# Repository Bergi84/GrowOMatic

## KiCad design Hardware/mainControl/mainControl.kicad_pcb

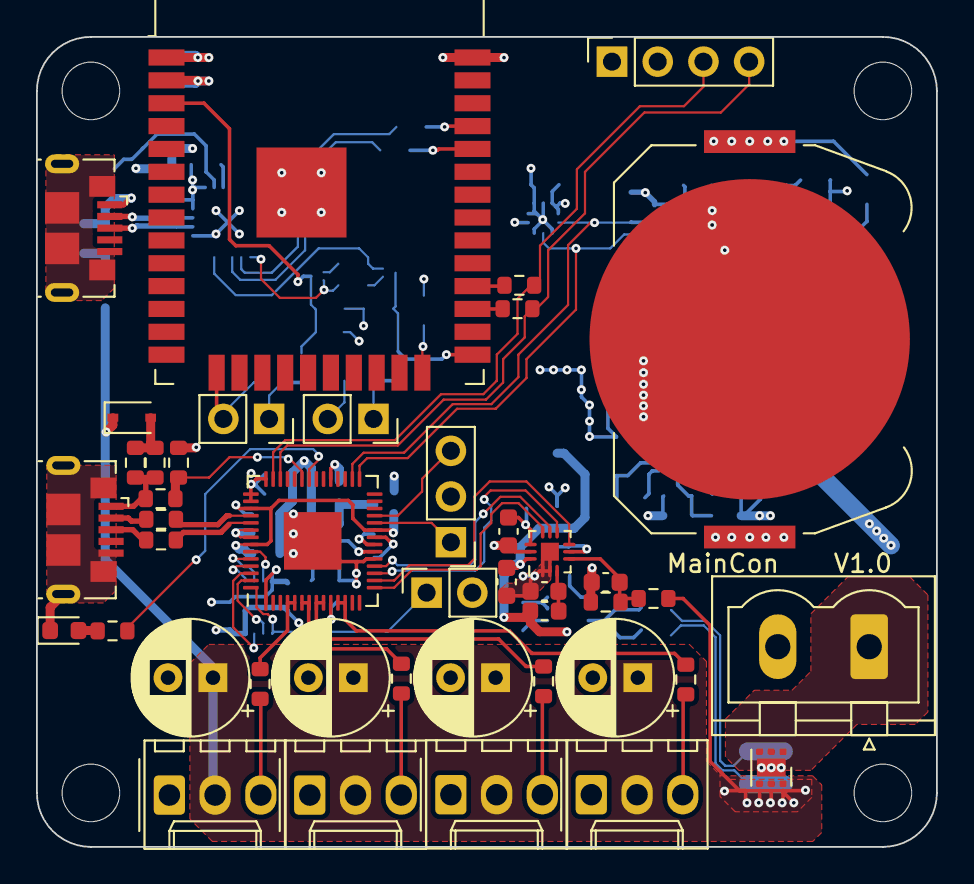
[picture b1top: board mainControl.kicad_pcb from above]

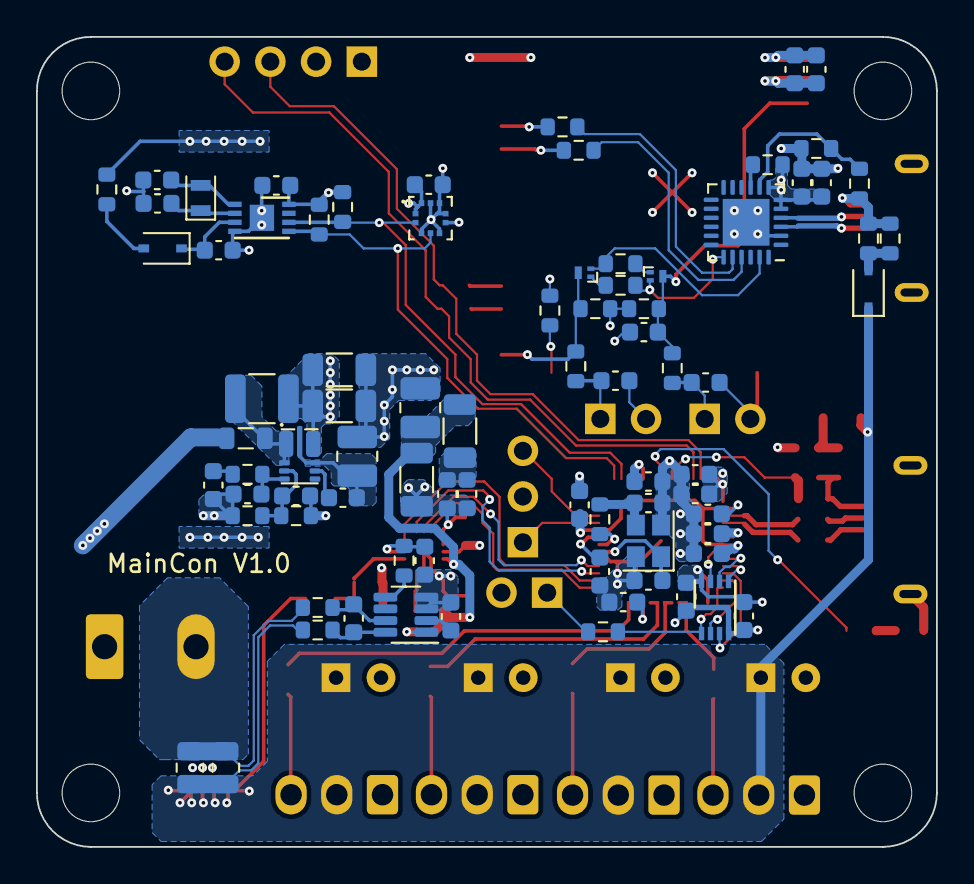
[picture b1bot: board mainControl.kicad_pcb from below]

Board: 4 copper layers, 50.0 x 45.0 mm, 128 parts (81 on the bottom side), 83 nets.

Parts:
BT1: Battery_Cell; BatteryHolder_Keystone_3034_1x20mm
C1, C2: 12p; C_0603_1608Metric
C3, C4, C12, C14, C15, C16, C17, C18, C21, C24, C27, C29, C34, C39, C41, C42, C43: 100nF; C_0603_1608Metric
C5, C11, C20: 100n; C_0603_1608Metric
C6, C7, C9, C10: 100µ; CP_Radial_D6.3mm_P2.50mm
C8, C23, C25: DNP; C_0603_1608Metric
C13: 10µ; C_1210_3225Metric
C19: 3.3n; C_0603_1608Metric
C22, C32, C37, C40: 1µF; C_0603_1608Metric
C26, C28: 10p; C_0603_1608Metric
C30: 100p; C_0603_1608Metric
C31, C33, C44, C45: 22µ; C_1206_3216Metric
C35, C36, C38: 1nF; C_0603_1608Metric
D1, D3, D4: BAT54W; D_SOD-323
D2: Green; LED_0603_1608Metric
H1, H2, H3, H4: MountingHole; MountingHole_3.2mm_M3_DIN965
J1, J10: USB_B_Micro; USB_Micro-B_GCT_USB3076-30-A
J2: Conn_01x03; PinHeader_1x03_P2.54mm_Vertical
J3, J11, J12: Conn_01x02; PinSocket_1x02_P2.54mm_Vertical
J4: Conn_01x02; PhoenixContact_MSTBVA_2,5_2-G-5,08_1x02_P5.08mm_Vertical
J5, J6, J7, J8: Conn_01x03; Molex_KK-254_AE-6410-03A_1x03_P2.54mm_Vertical
J9: Conn_01x04; PinSocket_1x04_P2.54mm_Vertical
L1: 1µ; L_0805_2012Metric
L2, L3: 4.7u; L_1008_2520Metric
Q1, Q2: MMBT3904LP; Diodes_DFN1006-3
R1, R2, R36, R37: 20R; R_0603_1608Metric
R3, R7, R8, R16, R17, R18, R19, R26: 1k; R_0603_1608Metric
R4, R5: 27; R_0603_1608Metric
R6, R15, R21, R22, R30, R31, R32, R40: 10k; R_0603_1608Metric
R9, R13: 0R; R_0603_1608Metric
R10, R34, R35: 470R; R_0603_1608Metric
R11, R12: 0R01; R_0805_2012Metric
R14: 5.6k; R_0603_1608Metric
R20: 1k5; R_0603_1608Metric
R23: 27k; R_0603_1608Metric
R24: 91k; R_0603_1608Metric
R25: 30k; R_0603_1608Metric
R27, R28, R41, R42: 470; R_0603_1608Metric
R29, R33: DNP; R_0603_1608Metric
R38: 22k; R_0603_1608Metric
R39: 47k; R_0603_1608Metric
R43: 0R; L_0603_1608Metric
R44, R45: 1R; L_0603_1608Metric
U1: W25Q16JVUXIQ; DFN-8-1EP_3x2mm_P0.5mm_EP0.3x1.6mm
U2: RP2040; QFN-56-1EP_7x7mm_P0.4mm_EP3.2x3.2mm
U3: INA186A3IDDF; SOT-23-8
U4: ILPS22QS; HLGA-10L
U5: AP63357Q; V-DFN3020-13
U6: MCP79410T-I/MNY; DFN-8-1EP_3x2mm_P0.5mm_EP1.36x1.46mm
U7: ESP32-WROOM-32
U8: CP2102N-Axx-xQFN24; QFN-24-1EP_4x4mm_P0.5mm_EP2.6x2.6mm
U9: TVS2700DRV; WSON-6-1EP_2x2mm_P0.65mm_EP1x1.6mm
U10: MCP3465R; QFN-12_EP_2x2_Pitch0.4mm
Y1: 12Mhz; Crystal_SMD_2520-4Pin_2.5x2.0mm
Y2: Crystal; Crystal_SMD_2012-2Pin_2.0x1.2mm

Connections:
+1V1: C16.1, C18.1, C22.1, U2.23 (DVDD), U2.45 (VREG_VOUT), U2.50 (DVDD)
+3.3V: C5.1, U3.2 (EN)
+3.3VA: C42.1, C44.2, C45.2, L3.2, R43.1, U3.1 (VS), U10.12 (AVDD)
+3V3: C4.1, C12.1, C14.1, C15.1, C17.1, C21.1, C24.1, C25.2, C27.1, C29.1, C31.2, C32.1, C33.2, C34.1, C37.1, C39.1, C40.1, C43.1, J9.2, L2.2, L3.1, R21.2, R22.2, R24.1, R29.2, R32.2, R33.2, R40.2, U1.8 (VCC), U2.1 (IOVDD), U2.10 (IOVDD), U2.22 (IOVDD), U2.33 (IOVDD), U2.42 (IOVDD), U2.43 (ADC_AVDD), U2.44 (VREG_IN), U2.48 (USB_VDD), U2.49 (IOVDD), U4.1 (VDD_IO), U4.6 (CS), U4.10 (VDD), U6.8 (VCC), U7.2 (VDD), U8.5 (VIO), U8.6 (VDD), U8.7 (VREGIN), U10.11 (DVDD)
+24V: C6.1, C7.1, C9.1, C10.1, D1.1 (K), D4.1 (K), J5.2, J6.2, J7.2, J8.2, L1.2, R6.2, R9.2, R11.1, R12.1, U9.4 (IN), U9.5 (IN), U9.6 (IN)
/ESP/DTR: Q2.2 (E), R30.1, U8.23 (~DTR)
/ESP/ESP_D+: J10.3 (D+), U8.3 (D+)
/ESP/ESP_D-: J10.2 (D-), U8.4 (D-)
/ESP/ESP_EN: C35.1, Q1.3 (C), R32.1, R35.1, U7.3 (EN)
/ESP/ESP_IO0: Q2.3 (C), R33.1, R34.1, U7.25 (IO0)
/ESP/ESP_RXD: R41.1, U7.34 (RXD0/IO3)
/ESP/ESP_TXD: R42.1, U7.35 (TXD0/IO1)
/ESP/RTS: Q1.2 (E), R31.1, U8.19 (~RTS)
/ESP/RXD: J9.3, R28.1, U2.41 (GPIO29_ADC3)
/ESP/TXD: J9.4, R27.1, U2.40 (GPIO28_ADC2)
/ESP/VBUS_ESP: J10.1 (VBUS), R36.2, R37.2, R38.2
/QSPI_CLK: U1.6 (CLK), U2.52 (QSPI_SCLK)
/QSPI_CS: R8.1, U1.1 (~CS), U2.56 (QSPI_SS)
/QSPI_D0: U1.5 (DI(IO0)), U2.53 (QSPI_SD0)
/QSPI_D1: U1.2 (DO(IO1)), U2.55 (QSPI_SD1)
/QSPI_D2: U1.3 (IO2), U2.54 (QSPI_SD2)
/QSPI_D3: U1.7 (IO3), U2.51 (QSPI_SD3)
/UART0: R19.2, U2.11 (GPIO8), U2.12 (GPIO9)
/UART1: R18.2, U2.8 (GPIO6), U2.9 (GPIO7)
/UART2: R17.2, U2.6 (GPIO4), U2.7 (GPIO5)
/UART3: R16.2, U2.4 (GPIO2), U2.5 (GPIO3)
/XIN: C1.1, U2.20 (XIN), Y1.1
/XOUT: R3.1, U2.21 (XOUT)
/pheri/24V_Isens: C11.1, R20.1, U10.5 (CH0)
/pheri/24V_Vsens: C3.1, R6.1, R7.2, U10.4 (CH1)
/pheri/CS: U2.16 (GPIO13), U10.6 (CS)
/pheri/SCK: U2.17 (GPIO14), U10.7 (SCK)
/pheri/SCL: R22.1, U2.30 (GPIO19), U4.2 (SCL/SPC), U6.6 (SCL)
/pheri/SDA: R21.1, U2.29 (GPIO18), U4.4 (SDA/SDIO), U6.5 (SDA)
/pheri/SDI: U2.18 (GPIO15), U10.8 (SDI)
/pheri/SDO: U2.15 (GPIO12), U10.9 (SDO)
GND: BT1.2 (-), C1.2, C2.2, C3.2, C4.2, C5.2, C6.2, C7.2, C9.2, C10.2, C11.2, C12.2, C13.1, C14.2, C15.2, C16.2, C17.2, C18.2, C19.1, C21.2, C22.2, C23.1, C24.2, C26.2, C27.2, C28.2, C29.2, C30.2, C31.1, C32.2, C33.1, C34.2, C35.2, C36.2, C37.2, C38.2, C39.2, C40.2, C41.2, C42.2, C43.2, C44.1, D2.1 (K), J1.5 (GND), J1.6 (Shield), J2.2, J3.2, J4.1, J5.1, J6.1, J7.1, J8.1, J9.1, J10.5 (GND), J10.6 (Shield), J11.2, J12.2, R7.1, R15.2, R25.2, R39.2, R44.2, R45.2, U1.4 (GND), U1.9 (EP), U2.19 (TESTEN), U2.57 (GND), U3.3 (REF), U3.4 (GND), U4.3 (RES), U4.5 (AH2), U4.7 (AH1), U4.8 (GND_IO), U4.9 (GND), U5.8 (GND), U6.4 (VSS), U6.9 (EP), U7.1 (GND), U7.15 (GND), U7.38 (GND), U7.39 (GND), U8.2 (GND), U8.25 (GND), U9.1 (GND), U9.2 (GND), U9.3 (GND), U9.7 (GND), U10.1 (AGND), U10.2 (REFIN-), U10.10 (DGND), U10.13 (EP), Y1.2, Y1.4
unnamed: BT1.1 (+), R26.1
unnamed: C2.1, R3.2, Y1.3
unnamed: C8.1, R9.1, U3.8 (-IN)
unnamed: C8.2, R13.1, U3.7 (+IN)
unnamed: C13.2, L1.1, U5.1 (VIN), U5.2 (EN)
unnamed: C19.2, R23.2
unnamed: C20.1, L2.1, U5.7 (NC), U5.9 (SW)
unnamed: C20.2, U5.6 (BST)
unnamed: C23.2, R23.1, U5.4 (COMP)
unnamed: C25.1, R24.2, R25.1, U5.3 (FB)
unnamed: C26.1, U6.2 (X2), Y2.1
unnamed: C28.1, U6.1 (X1), Y2.2
unnamed: C30.1, D3.1 (K), U6.3 (VBAT)
unnamed: C36.1, J11.1, R34.2
unnamed: C38.1, J12.1, R35.2
unnamed: C41.1, R43.2, U10.3 (REFIN+)
unnamed: C45.1, R44.1, R45.1
unnamed: D1.2 (A), R1.1, R2.1
unnamed: D2.2 (A), R10.2
unnamed: D3.2 (A), R26.2
unnamed: D4.2 (A), R36.1, R37.1
unnamed: J1.2 (D-), R5.1
unnamed: J1.3 (D+), R4.1
unnamed: J2.1, U2.24 (SWCLK)
unnamed: J2.3, U2.25 (SWD)
unnamed: J3.1, R8.2
unnamed: J4.2, R11.2, R12.2, R13.2
unnamed: J5.3, R16.1
unnamed: J6.3, R17.1
unnamed: J7.3, R18.1
unnamed: J8.3, R19.1
unnamed: Q1.1 (B), R30.2
unnamed: Q2.1 (B), R31.2
unnamed: R4.2, U2.47 (USB_DP)
unnamed: R5.2, U2.46 (USB_DM)
unnamed: R10.1, U2.36 (GPIO24)
unnamed: R14.2, R15.1, U2.37 (GPIO25)
unnamed: R20.2, U3.5 (OUT)
unnamed: R27.2, U7.27 (IO16)
unnamed: R28.2, U7.28 (IO17)
unnamed: R29.1, U7.24 (IO2)
unnamed: R38.1, R39.1, U8.8 (VBUS)
unnamed: R40.1, U8.9 (~RST)
unnamed: R41.2, U8.21 (TXD)
unnamed: R42.2, U8.20 (RXD)
VBUS: J1.1 (VBUS), R1.2, R2.2, R14.1

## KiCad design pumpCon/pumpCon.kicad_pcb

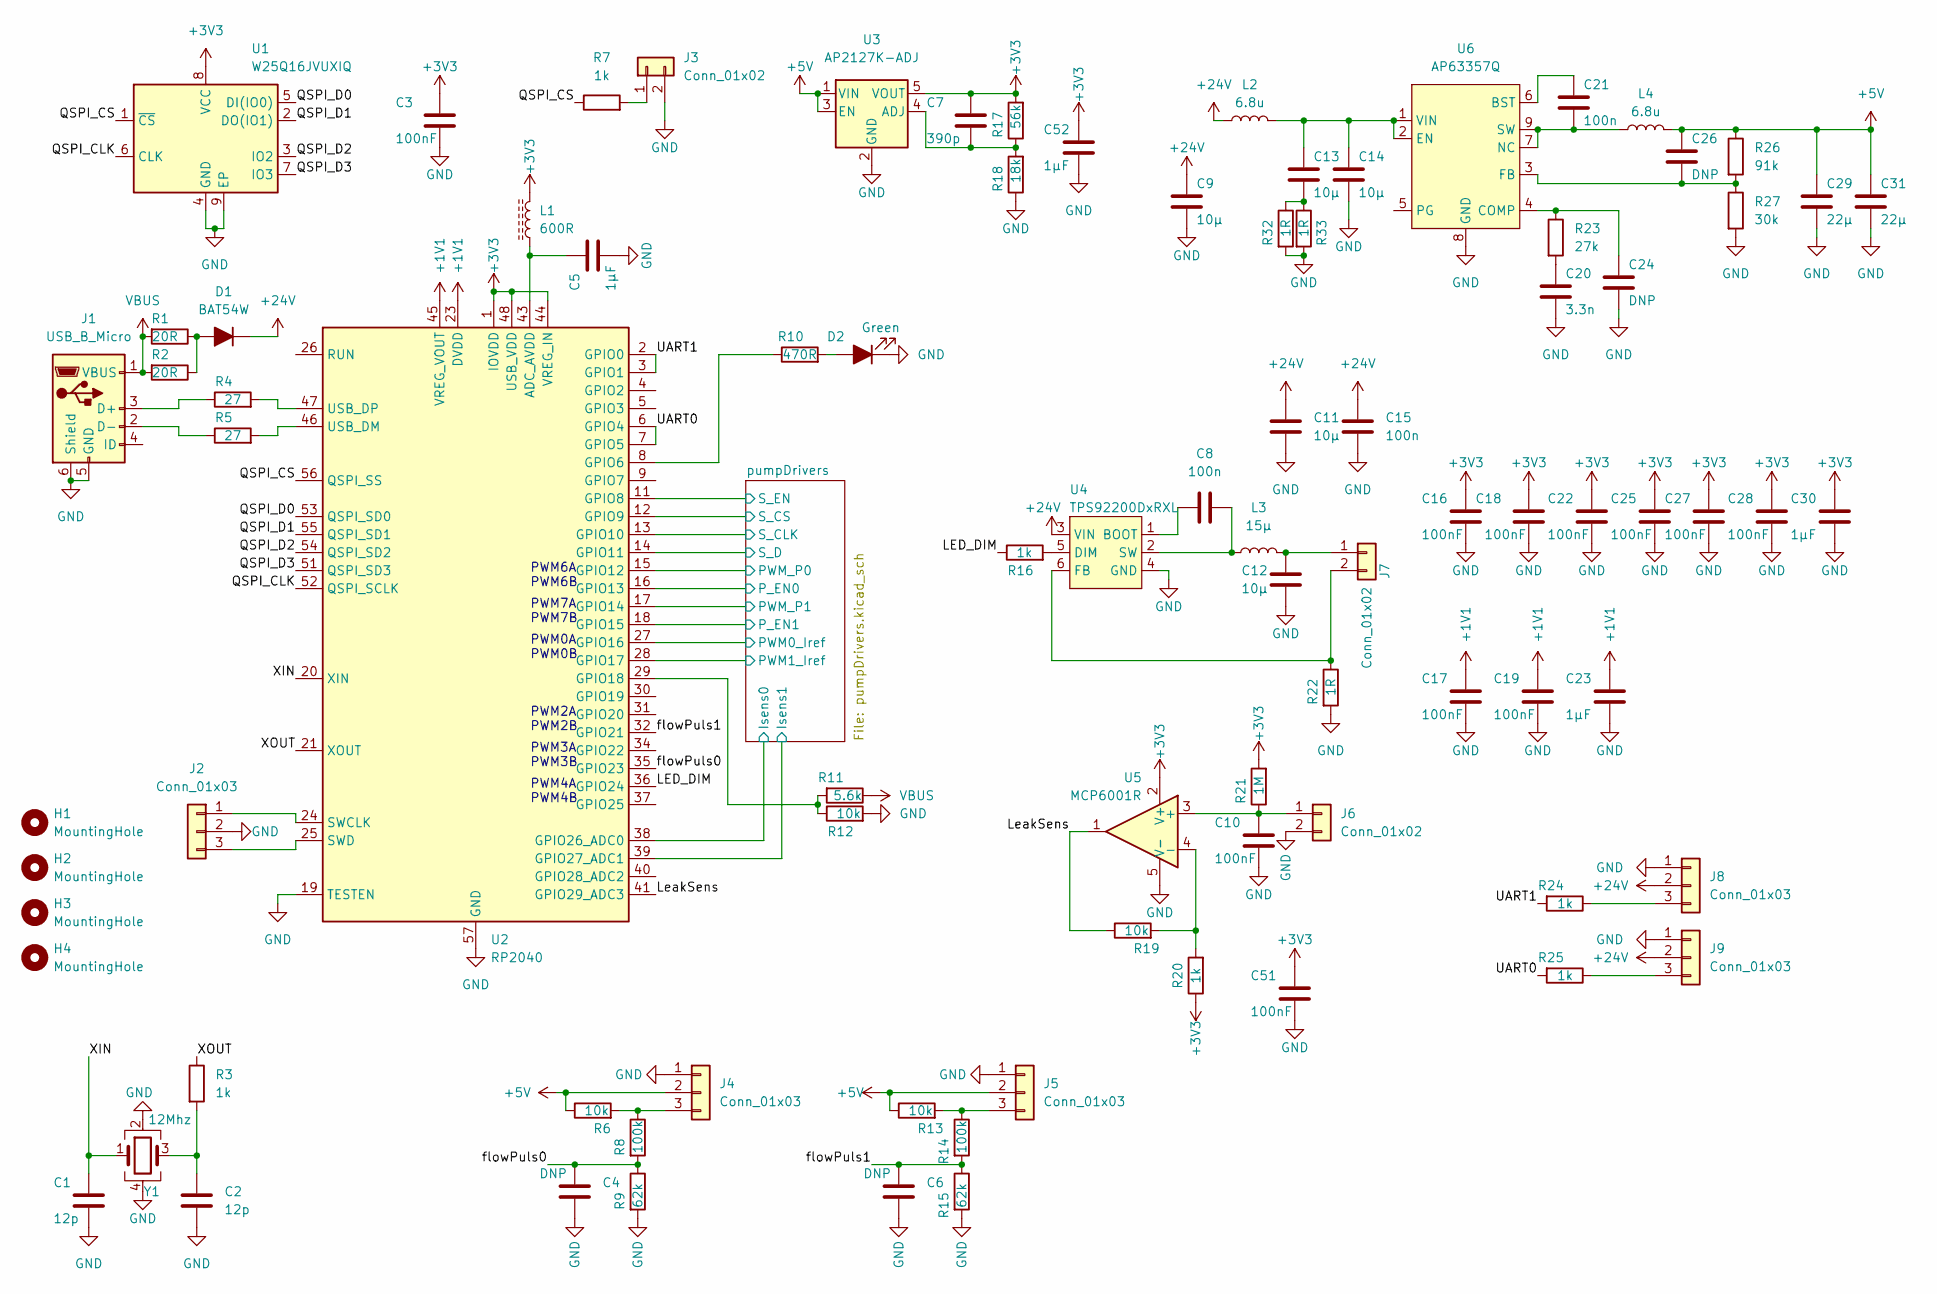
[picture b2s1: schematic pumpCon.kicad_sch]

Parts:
C1, C2: 12p; C_0603_1608Metric
C3, C10, C16, C17, C18, C19, C22, C25, C27, C28, C51: 100nF; C_0603_1608Metric
C4, C6, C24, C26: DNP; C_0603_1608Metric
C5, C23, C30, C52: 1µF; C_0603_1608Metric
C7: 390p; C_0603_1608Metric
C8, C15, C21: 100n; C_0603_1608Metric
C9, C13, C14: 10µ; C_1210_3225Metric
C11, C12: 10µ; C_1210_3225Metric; Voltage 50V
C20: 3.3n; C_0603_1608Metric
C29, C31: 22µ; C_1206_3216Metric
D1: BAT54W; D_SOD-323
D2: Green; LED_0603_1608Metric
H1, H2, H3, H4: MountingHole; MountingHole_3.2mm_M3_DIN965
J1: USB_B_Micro; USB_Micro-B_GCT_USB3076-30-A
J2: Conn_01x03; PinHeader_1x03_P2.54mm_Vertical
J3: Conn_01x02; PinSocket_1x02_P2.54mm_Vertical
J4, J5: Conn_01x03; JST_EH_B3B-EH-A_1x03_P2.50mm_Vertical
J6, J7: Conn_01x02; JST_EH_B2B-EH-A_1x02_P2.50mm_Vertical
J8, J9: Conn_01x03; Molex_KK-254_AE-6410-03A_1x03_P2.54mm_Vertical
L1: 600R; L_0603_1608Metric
L2, L4: 6.8u; L_Taiyo-Yuden_NR-30xx
L3: 15µ; L_Taiyo-Yuden_NR-50xx
R1, R2: 20R; R_0603_1608Metric
R3, R7, R16, R20, R24, R25: 1k; R_0603_1608Metric
R4, R5: 27; R_0603_1608Metric
R6, R12, R13, R19: 10k; R_0603_1608Metric
R8, R14: 100k; R_0603_1608Metric
R9, R15: 62k; R_0603_1608Metric
R10: 470R; R_0603_1608Metric
R11: 5.6k; R_0603_1608Metric
R17: 56k; R_0603_1608Metric
R18: 18k; R_0603_1608Metric
R21: 1M; R_0603_1608Metric
R22, R32, R33: 1R; R_0603_1608Metric
R23: 27k; R_0603_1608Metric
R26: 91k; R_0603_1608Metric
R27: 30k; R_0603_1608Metric
U1: W25Q16JVUXIQ; DFN-8-1EP_3x2mm_P0.5mm_EP0.3x1.6mm
U2: RP2040; QFN-56-1EP_7x7mm_P0.4mm_EP3.2x3.2mm
U3: AP2127K-ADJ; SOT-23-5
U4: TPS92200DxRXL; VQFN-HR
U5: MCP6001R; SOT-23-5
U6: AP63357Q; V-DFN3020-13
Y1: 12Mhz; Crystal_SMD_2520-4Pin_2.5x2.0mm

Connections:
+1V1: C17.1, C19.1, C23.1, U2.23 (DVDD), U2.45 (VREG_VOUT), U2.50 (DVDD)
+3V3: C3.1, C7.1, C16.1, C18.1, C22.1, C25.1, C27.1, C28.1, C30.1, C51.1, C52.1, L1.2, R17.2, R20.1, R21.2, U1.8 (VCC), U2.1 (IOVDD), U2.10 (IOVDD), U2.22 (IOVDD), U2.33 (IOVDD), U2.42 (IOVDD), U2.44 (VREG_IN), U2.48 (USB_VDD), U2.49 (IOVDD), U3.5 (VOUT), U5.2 (V+); also elsewhere on the board
+5V: C26.2, C29.2, C31.2, J4.2, J5.2, L4.2, R6.1, R13.1, R26.1, U3.1 (VIN), U3.3 (EN); also elsewhere on the board
+24V: C9.2, C11.2, C15.2, D1.1 (K), J8.2, J9.2, L2.1, U4.3 (VIN); also elsewhere on the board
/LED_DIM: R16.1, U2.36 (GPIO24)
/LeakSens: R19.1, U2.41 (GPIO29_ADC3), U5.1
/QSPI_CLK: U1.6 (CLK), U2.52 (QSPI_SCLK)
/QSPI_CS: R7.1, U1.1 (~CS), U2.56 (QSPI_SS)
/QSPI_D0: U1.5 (DI(IO0)), U2.53 (QSPI_SD0)
/QSPI_D1: U1.2 (DO(IO1)), U2.55 (QSPI_SD1)
/QSPI_D2: U1.3 (IO2), U2.54 (QSPI_SD2)
/QSPI_D3: U1.7 (IO3), U2.51 (QSPI_SD3)
/UART0: R25.2, U2.6 (GPIO4), U2.7 (GPIO5)
/UART1: R24.2, U2.2 (GPIO0), U2.3 (GPIO1)
/XIN: C1.1, U2.20 (XIN), Y1.1
/XOUT: R3.1, U2.21 (XOUT)
/flowPuls0: C4.1, R8.2, R9.1, U2.35 (GPIO23)
/flowPuls1: C6.1, R14.2, R15.1, U2.32 (GPIO21)
/pumpDrivers/Isens0: U2.38 (GPIO26_ADC0); also elsewhere on the board
/pumpDrivers/Isens1: U2.39 (GPIO27_ADC1); also elsewhere on the board
/pumpDrivers/PWM0_Iref: U2.27 (GPIO16); also elsewhere on the board
/pumpDrivers/PWM1_Iref: U2.28 (GPIO17); also elsewhere on the board
/pumpDrivers/PWM_P0: U2.15 (GPIO12); also elsewhere on the board
/pumpDrivers/PWM_P1: U2.17 (GPIO14); also elsewhere on the board
/pumpDrivers/S_CLK: U2.13 (GPIO10); also elsewhere on the board
/pumpDrivers/S_CS: U2.12 (GPIO9); also elsewhere on the board
/pumpDrivers/S_D: U2.14 (GPIO11); also elsewhere on the board
/pumpDrivers/S_EN: U2.11 (GPIO8); also elsewhere on the board
GND: C1.2, C2.2, C3.2, C4.2, C5.2, C6.2, C9.1, C10.2, C11.1, C12.1, C14.1, C15.1, C16.2, C17.2, C18.2, C19.2, C20.1, C22.2, C23.2, C24.1, C25.2, C27.2, C28.2, C29.1, C30.2, C31.1, C51.2, C52.2, D2.1 (K), J1.5 (GND), J1.6 (Shield), J2.2, J3.2, J4.1, J5.1, J6.2, J8.1, J9.1, R9.2, R12.2, R15.2, R18.1, R22.2, R27.2, R32.2, R33.2, U1.4 (GND), U1.9 (EP), U2.19 (TESTEN), U2.57 (GND), U3.2 (GND), U4.4 (GND), U5.5 (V-), U6.8 (GND), Y1.2, Y1.4; also elsewhere on the board
unnamed: C2.1, R3.2, Y1.3
unnamed: C5.1, L1.1, U2.43 (ADC_AVDD)
unnamed: C7.2, R17.1, R18.2, U3.4 (ADJ)
unnamed: C8.1, U4.1 (BOOT)
unnamed: C8.2, L3.1, U4.2 (SW)
unnamed: C10.1, J6.1, R21.1, U5.3 (+)
unnamed: C12.2, J7.1, L3.2
unnamed: C13.1, R32.1, R33.1
unnamed: C13.2, C14.2, L2.2, U6.1 (VIN), U6.2 (EN)
unnamed: C20.2, R23.2
unnamed: C21.1, L4.1, U6.7 (NC), U6.9 (SW)
unnamed: C21.2, U6.6 (BST)
unnamed: C24.2, R23.1, U6.4 (COMP)
unnamed: C26.1, R26.2, R27.1, U6.3 (FB)
unnamed: D1.2 (A), R1.1, R2.1
unnamed: D2.2 (A), R10.2
unnamed: J1.2 (D-), R5.1
unnamed: J1.3 (D+), R4.1
unnamed: J2.1, U2.24 (SWCLK)
unnamed: J2.3, U2.25 (SWD)
unnamed: J3.1, R7.2
unnamed: J4.3, R6.2, R8.1
unnamed: J5.3, R13.2, R14.1
unnamed: J7.2, R22.1, U4.6 (FB)
unnamed: J8.3, R24.1
unnamed: J9.3, R25.1
unnamed: R4.2, U2.47 (USB_DP)
unnamed: R5.2, U2.46 (USB_DM)
unnamed: R16.2, U4.5 (DIM)
unnamed: R19.2, R20.2, U5.4 (-)
unnamed: R10.1, U2.8 (GPIO6)
unnamed: R11.2, R12.1, U2.29 (GPIO18)
VBUS: J1.1 (VBUS), R1.2, R2.2, R11.1

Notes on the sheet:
PWM3A PWM3B
PWM6A PWM6B
PWM7A PWM7B
PWM0A PWM0B
PWM4A PWM4B
PWM2A PWM2B

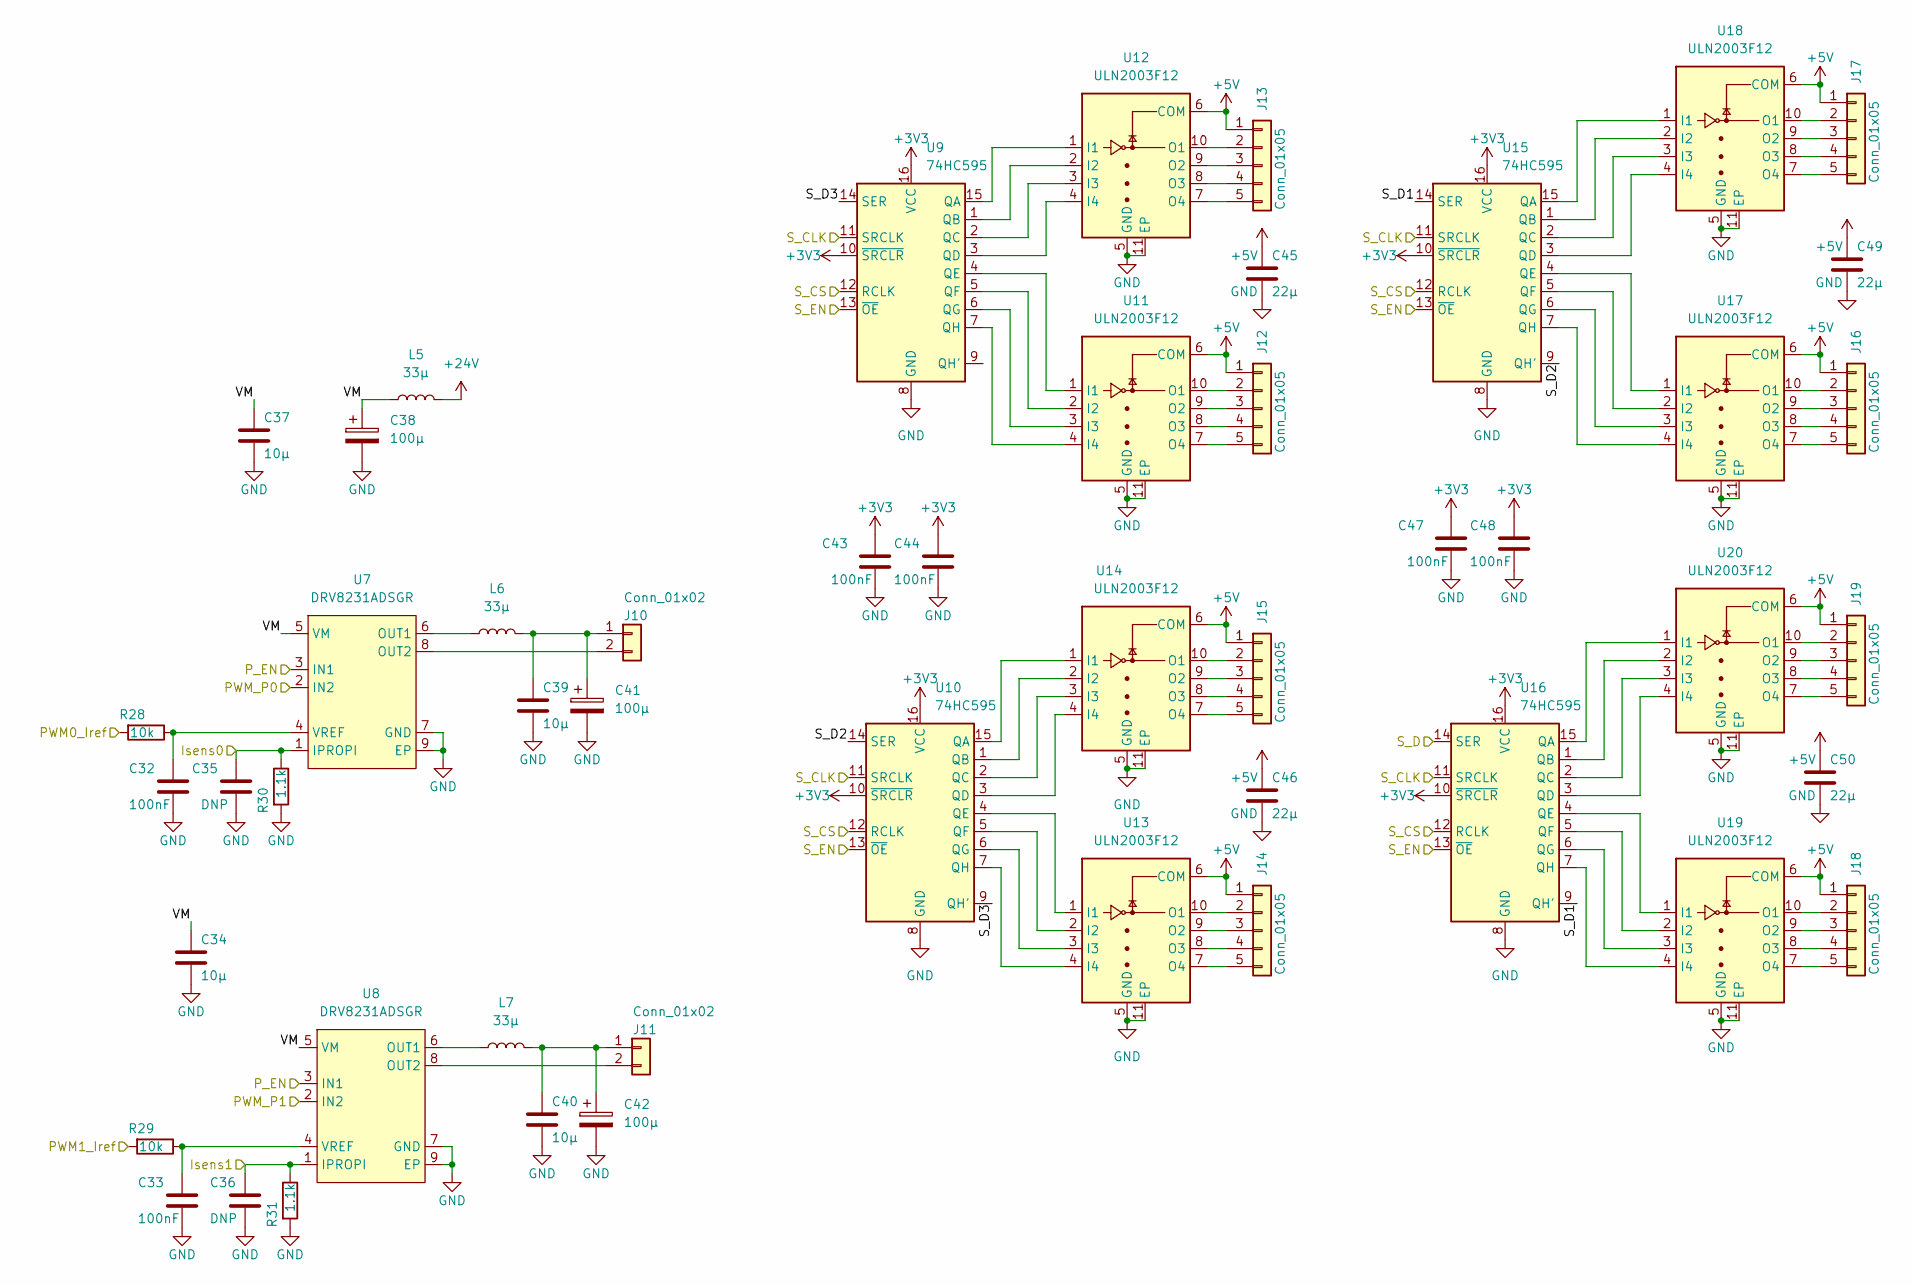
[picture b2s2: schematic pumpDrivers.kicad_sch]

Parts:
C32, C33, C43, C44, C47, C48: 100nF; C_0603_1608Metric
C34, C37, C39, C40: 10µ; C_1210_3225Metric
C35, C36: DNP; C_0603_1608Metric
C38, C41, C42: 100µ; CP_Radial_D6.3mm_P2.50mm
C45, C46, C49, C50: 22µ; C_1206_3216Metric
J10, J11: Conn_01x02; Molex_KK-254_AE-6410-02A_1x02_P2.54mm_Vertical
J12, J13, J14, J15, J16, J17, J18, J19: Conn_01x05; JST_EH_B5B-EH-A_1x05_P2.50mm_Vertical
L5, L6, L7: 33µ; L_12x12mm_H8mm
R28, R29: 10k; R_0603_1608Metric
R30, R31: 1.1k; R_0603_1608Metric
U7, U8: DRV8231ADSGR; WSON-8-1EP_2x2mm_P0.5mm_EP0.9x1.6mm
U9, U10, U15, U16: 74HC595; TSSOP-16_4.4x5mm_P0.65mm
U11, U12, U13, U14, U17, U18, U19, U20: ULN2003F12; DFN-10-1EP_3x3mm_P0.5mm_EP1.7x2.5mm

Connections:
+3V3: C43.1, C44.1, C47.1, C48.1, U9.10 (~SRCLR), U9.16 (VCC), U10.10 (~SRCLR), U10.16 (VCC), U15.10 (~SRCLR), U15.16 (VCC), U16.10 (~SRCLR), U16.16 (VCC); also elsewhere on the board
+5V: C45.2, C46.2, C49.2, C50.2, J12.1, J13.1, J14.1, J15.1, J16.1, J17.1, J18.1, J19.1, U11.6 (COM), U12.6 (COM), U13.6 (COM), U14.6 (COM), U17.6 (COM), U18.6 (COM), U19.6 (COM), U20.6 (COM); also elsewhere on the board
+24V: L5.2; also elsewhere on the board
/pumpDrivers/Isens0: C35.1, R30.1, U7.1 (IPROPI); also elsewhere on the board
/pumpDrivers/Isens1: C36.1, R31.1, U8.1 (IPROPI); also elsewhere on the board
/pumpDrivers/PWM0_Iref: R28.2; also elsewhere on the board
/pumpDrivers/PWM1_Iref: R29.2; also elsewhere on the board
/pumpDrivers/PWM_P0: U7.2 (IN2); also elsewhere on the board
/pumpDrivers/PWM_P1: U8.2 (IN2); also elsewhere on the board
/pumpDrivers/S_CLK: U9.11 (SRCLK), U10.11 (SRCLK), U15.11 (SRCLK), U16.11 (SRCLK); also elsewhere on the board
/pumpDrivers/S_CS: U9.12 (RCLK), U10.12 (RCLK), U15.12 (RCLK), U16.12 (RCLK); also elsewhere on the board
/pumpDrivers/S_D: U16.14 (SER); also elsewhere on the board
/pumpDrivers/S_D1: U15.14 (SER), U16.9 (QH')
/pumpDrivers/S_D2: U10.14 (SER), U15.9 (QH')
/pumpDrivers/S_D3: U9.14 (SER), U10.9 (QH')
/pumpDrivers/S_EN: U9.13 (~OE), U10.13 (~OE), U15.13 (~OE), U16.13 (~OE); also elsewhere on the board
/pumpDrivers/VM: C34.2, C37.2, C38.1, L5.1, U7.5 (VM), U8.5 (VM)
GND: C32.2, C33.2, C34.1, C35.2, C36.2, C37.1, C38.2, C39.1, C40.1, C41.2, C42.2, C43.2, C44.2, C45.1, C46.1, C47.2, C48.2, C49.1, C50.1, R30.2, R31.2, U7.7 (GND), U7.9 (EP), U8.7 (GND), U8.9 (EP), U9.8 (GND), U10.8 (GND), U11.5 (GND), U11.11 (EP), U12.5 (GND), U12.11 (EP), U13.5 (GND), U13.11 (EP), U14.5 (GND), U14.11 (EP), U15.8 (GND), U16.8 (GND), U17.5 (GND), U17.11 (EP), U18.5 (GND), U18.11 (EP), U19.5 (GND), U19.11 (EP), U20.5 (GND), U20.11 (EP); also elsewhere on the board
unnamed: C32.1, R28.1, U7.4 (VREF)
unnamed: C33.1, R29.1, U8.4 (VREF)
unnamed: C39.2, C41.1, J10.1, L6.2
unnamed: C40.2, C42.1, J11.1, L7.2
unnamed: J10.2, U7.8 (OUT2)
unnamed: J11.2, U8.8 (OUT2)
unnamed: J12.2, U11.10 (O1)
unnamed: J12.3, U11.9 (O2)
unnamed: J12.4, U11.8 (O3)
unnamed: J12.5, U11.7 (O4)
unnamed: J13.2, U12.10 (O1)
unnamed: J13.3, U12.9 (O2)
unnamed: J13.4, U12.8 (O3)
unnamed: J13.5, U12.7 (O4)
unnamed: J14.2, U13.10 (O1)
unnamed: J14.3, U13.9 (O2)
unnamed: J14.4, U13.8 (O3)
unnamed: J14.5, U13.7 (O4)
unnamed: J15.2, U14.10 (O1)
unnamed: J15.3, U14.9 (O2)
unnamed: J15.4, U14.8 (O3)
unnamed: J15.5, U14.7 (O4)
unnamed: J16.2, U17.10 (O1)
unnamed: J16.3, U17.9 (O2)
unnamed: J16.4, U17.8 (O3)
unnamed: J16.5, U17.7 (O4)
unnamed: J17.2, U18.10 (O1)
unnamed: J17.3, U18.9 (O2)
unnamed: J17.4, U18.8 (O3)
unnamed: J17.5, U18.7 (O4)
unnamed: J18.2, U19.10 (O1)
unnamed: J18.3, U19.9 (O2)
unnamed: J18.4, U19.8 (O3)
unnamed: J18.5, U19.7 (O4)
unnamed: J19.2, U20.10 (O1)
unnamed: J19.3, U20.9 (O2)
unnamed: J19.4, U20.8 (O3)
unnamed: J19.5, U20.7 (O4)
unnamed: L6.1, U7.6 (OUT1)
unnamed: L7.1, U8.6 (OUT1)
unnamed: U10.1 (QB), U14.2 (I2)
unnamed: U10.2 (QC), U14.3 (I3)
unnamed: U10.3 (QD), U14.4 (I4)
unnamed: U10.4 (QE), U13.1 (I1)
unnamed: U10.5 (QF), U13.2 (I2)
unnamed: U10.6 (QG), U13.3 (I3)
unnamed: U10.7 (QH), U13.4 (I4)
unnamed: U10.15 (QA), U14.1 (I1)
unnamed: U9.4 (QE), U11.1 (I1)
unnamed: U9.5 (QF), U11.2 (I2)
unnamed: U9.6 (QG), U11.3 (I3)
unnamed: U9.7 (QH), U11.4 (I4)
unnamed: U9.15 (QA), U12.1 (I1)
unnamed: U9.1 (QB), U12.2 (I2)
unnamed: U9.2 (QC), U12.3 (I3)
unnamed: U9.3 (QD), U12.4 (I4)
unnamed: U15.1 (QB), U18.2 (I2)
unnamed: U15.2 (QC), U18.3 (I3)
unnamed: U15.3 (QD), U18.4 (I4)
unnamed: U15.4 (QE), U17.1 (I1)
unnamed: U15.5 (QF), U17.2 (I2)
unnamed: U15.6 (QG), U17.3 (I3)
unnamed: U15.7 (QH), U17.4 (I4)
unnamed: U15.15 (QA), U18.1 (I1)
unnamed: U16.1 (QB), U20.2 (I2)
unnamed: U16.2 (QC), U20.3 (I3)
unnamed: U16.3 (QD), U20.4 (I4)
unnamed: U16.4 (QE), U19.1 (I1)
unnamed: U16.5 (QF), U19.2 (I2)
unnamed: U16.6 (QG), U19.3 (I3)
unnamed: U16.7 (QH), U19.4 (I4)
unnamed: U16.15 (QA), U20.1 (I1)

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
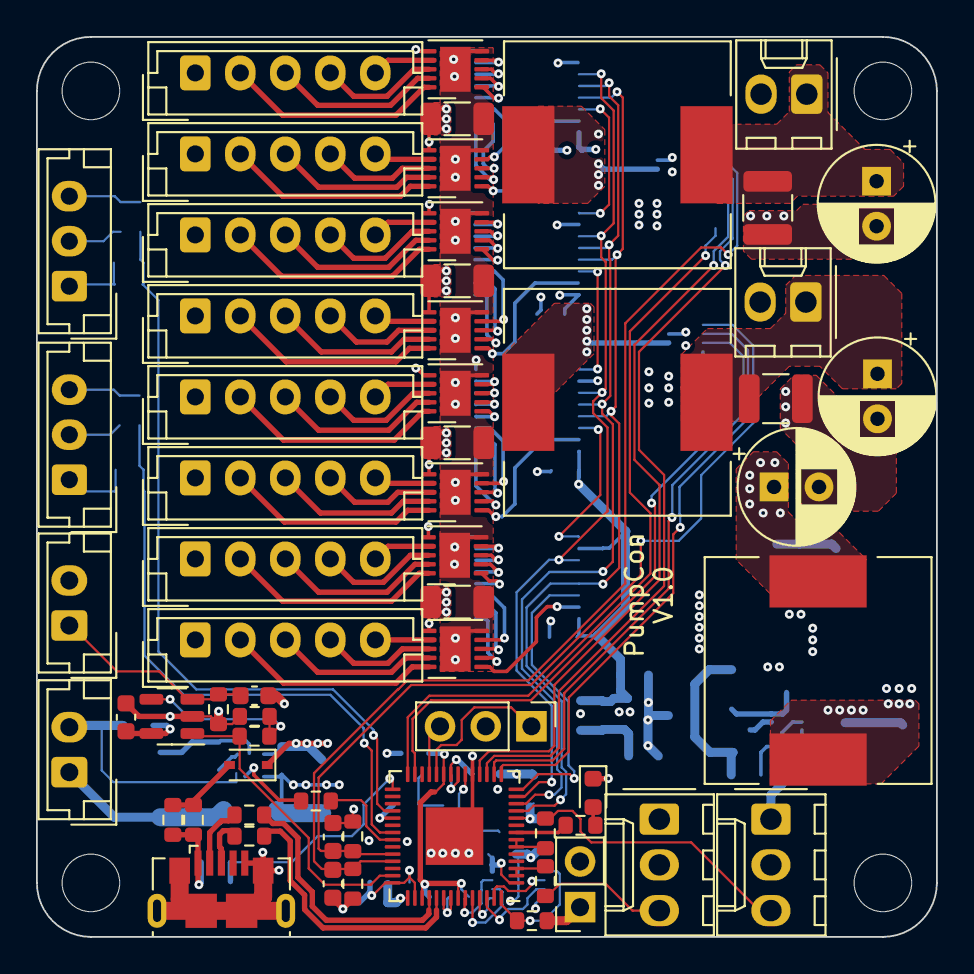
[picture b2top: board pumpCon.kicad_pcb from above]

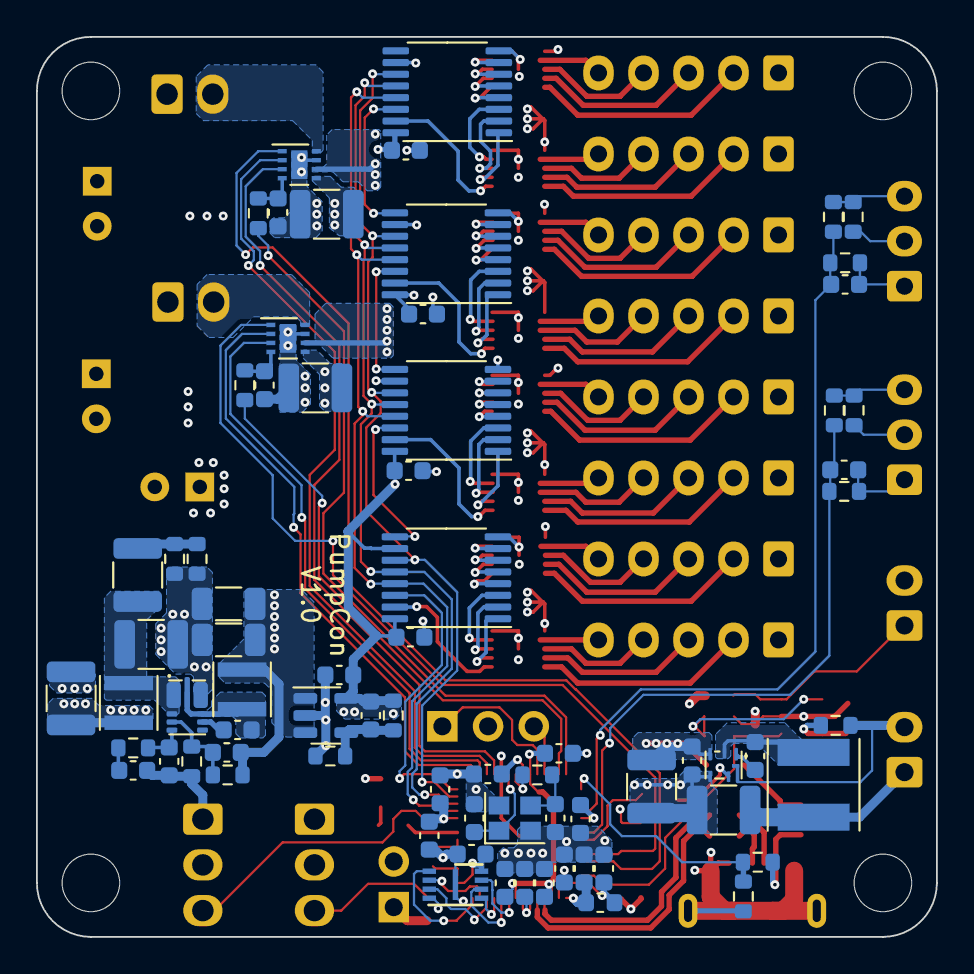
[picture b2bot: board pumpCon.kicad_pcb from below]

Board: 4 copper layers, 50.0 x 50.0 mm, 138 parts (73 on the bottom side), 140 nets.

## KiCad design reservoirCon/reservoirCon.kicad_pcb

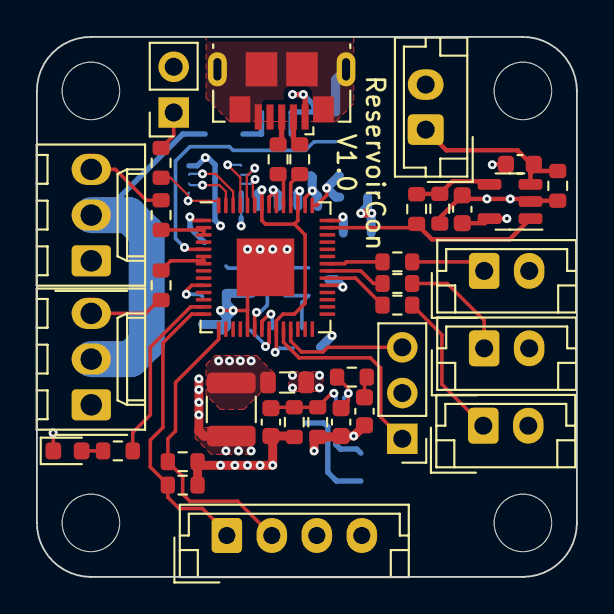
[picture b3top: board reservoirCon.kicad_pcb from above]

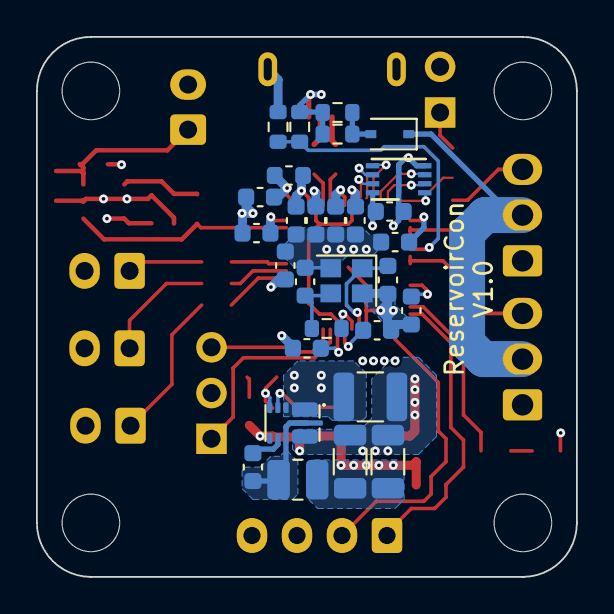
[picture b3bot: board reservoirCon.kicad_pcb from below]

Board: 4 copper layers, 30.0 x 30.0 mm, 70 parts (29 on the bottom side), 47 nets.

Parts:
C1, C2: 12p; C_0603_1608Metric
C3, C6, C8, C9, C10, C11, C14, C17, C19, C20, C24: 100nF; C_0603_1608Metric
C4, C15, C22: 1µF; C_0603_1608Metric
C5, C7: 10µ; C_1210_3225Metric
C12: 3.3n; C_0603_1608Metric
C13: 100n; C_0603_1608Metric
C16, C18: DNP; C_0603_1608Metric
C21, C23: 22µ; C_1206_3216Metric
D1: BAT54W; D_SOD-323
D2: Green; LED_0603_1608Metric
H1, H2, H3, H4: MountingHole; MountingHole_3.2mm_M3_DIN965
J1: USB_B_Micro; USB_Micro-B_GCT_USB3076-30-A
J2: Conn_01x03; PinHeader_1x03_P2.54mm_Vertical
J3: Conn_01x02; PinSocket_1x02_P2.54mm_Vertical
J4: Conn_01x04; JST_EH_B4B-EH-A_1x04_P2.50mm_Vertical
J5, J6: Conn_01x03; Molex_KK-254_AE-6410-03A_1x03_P2.54mm_Vertical
J7, J8, J9, J10: Conn_01x02; JST_EH_B2B-EH-A_1x02_P2.50mm_Vertical
L1: 600R; L_0603_1608Metric
L2: 10µ; L_0805_2012Metric
L3: 4.7u; L_1008_2520Metric
R1, R2: 20R; R_0603_1608Metric
R3, R6, R10, R11, R15, R16, R17, R19: 1k; R_0603_1608Metric
R4, R5: 27; R_0603_1608Metric
R7: 470R; R_0603_1608Metric
R8, R9, R13, R14: 10k; R_0603_1608Metric
R12: 5.6k; R_0603_1608Metric
R18: 1M; R_0603_1608Metric
R20: 27k; R_0603_1608Metric
R21: 91k; R_0603_1608Metric
R22: 30k; R_0603_1608Metric
U1: W25Q16JVUXIQ; DFN-8-1EP_3x2mm_P0.5mm_EP0.3x1.6mm
U2: RP2040; QFN-56-1EP_7x7mm_P0.4mm_EP3.2x3.2mm
U3: MCP6001R; SOT-23-5
U4: AP63357Q; V-DFN3020-13
Y1: 12Mhz; Crystal_SMD_2520-4Pin_2.5x2.0mm

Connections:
+1V1: C9.1, C11.1, C15.1, U2.23 (DVDD), U2.45 (VREG_VOUT), U2.50 (DVDD)
+3V3: C3.1, C8.1, C10.1, C14.1, C17.1, C18.2, C19.1, C20.1, C21.2, C22.1, C23.2, C24.1, J4.4, L1.2, L3.2, R8.2, R9.2, R17.1, R18.2, R21.1, U1.8 (VCC), U2.1 (IOVDD), U2.10 (IOVDD), U2.22 (IOVDD), U2.33 (IOVDD), U2.42 (IOVDD), U2.44 (VREG_IN), U2.48 (USB_VDD), U2.49 (IOVDD), U3.2 (V+)
+24V: C5.2, D1.1 (K), J5.2, J6.2, L2.2
/DIN1: R15.1, U2.36 (GPIO24)
/DIN2: R16.1, U2.35 (GPIO23)
/DIN3: R19.1, U2.34 (GPIO22)
/LED: R7.1, U2.13 (GPIO10)
/LeakSens: R14.1, U2.41 (GPIO29_ADC3), U3.1
/QSPI_CLK: U1.6 (CLK), U2.52 (QSPI_SCLK)
/QSPI_CS: R6.1, U1.1 (~CS), U2.56 (QSPI_SS)
/QSPI_D0: U1.5 (DI(IO0)), U2.53 (QSPI_SD0)
/QSPI_D1: U1.2 (DO(IO1)), U2.55 (QSPI_SD1)
/QSPI_D2: U1.3 (IO2), U2.54 (QSPI_SD2)
/QSPI_D3: U1.7 (IO3), U2.51 (QSPI_SD3)
/UART0: R11.2, U2.6 (GPIO4), U2.7 (GPIO5)
/UART1: R10.2, U2.2 (GPIO0), U2.3 (GPIO1)
/XIN: C1.1, U2.20 (XIN), Y1.1
/XOUT: R3.1, U2.21 (XOUT)
GND: C1.2, C2.2, C3.2, C4.2, C5.1, C6.2, C7.1, C8.2, C9.2, C10.2, C11.2, C12.1, C14.2, C15.2, C16.1, C17.2, C19.2, C20.2, C21.1, C22.2, C23.1, C24.2, D2.1 (K), J1.5 (GND), J1.6 (Shield), J2.2, J3.2, J4.3, J5.1, J6.1, J7.2, J8.2, J9.2, J10.2, R13.2, R22.2, U1.4 (GND), U1.9 (EP), U2.19 (TESTEN), U2.57 (GND), U3.5 (V-), U4.8 (GND), Y1.2, Y1.4
unnamed: C2.1, R3.2, Y1.3
unnamed: C4.1, L1.1, U2.43 (ADC_AVDD)
unnamed: C6.1, J10.1, R18.1, U3.3 (+)
unnamed: C7.2, L2.1, U4.1 (VIN), U4.2 (EN)
unnamed: C12.2, R20.2
unnamed: C13.1, L3.1, U4.7 (NC), U4.9 (SW)
unnamed: C13.2, U4.6 (BST)
unnamed: C16.2, R20.1, U4.4 (COMP)
unnamed: C18.1, R21.2, R22.1, U4.3 (FB)
unnamed: D1.2 (A), R1.1, R2.1
unnamed: D2.2 (A), R7.2
unnamed: J1.2 (D-), R5.1
unnamed: J1.3 (D+), R4.1
unnamed: J2.1, U2.24 (SWCLK)
unnamed: J2.3, U2.25 (SWD)
unnamed: J3.1, R6.2
unnamed: J4.1, R9.1, U2.14 (GPIO11)
unnamed: J4.2, R8.1, U2.15 (GPIO12)
unnamed: J5.3, R10.1
unnamed: J6.3, R11.1
unnamed: J7.1, R15.2
unnamed: J8.1, R16.2
unnamed: R4.2, U2.47 (USB_DP)
unnamed: R5.2, U2.46 (USB_DM)
unnamed: R12.2, R13.1, U2.5 (GPIO3)
unnamed: R14.2, R17.2, U3.4 (-)
unnamed: J9.1, R19.2
VBUS: J1.1 (VBUS), R1.2, R2.2, R12.1
